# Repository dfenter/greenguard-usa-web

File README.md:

# greenguard-usa-web
website repository

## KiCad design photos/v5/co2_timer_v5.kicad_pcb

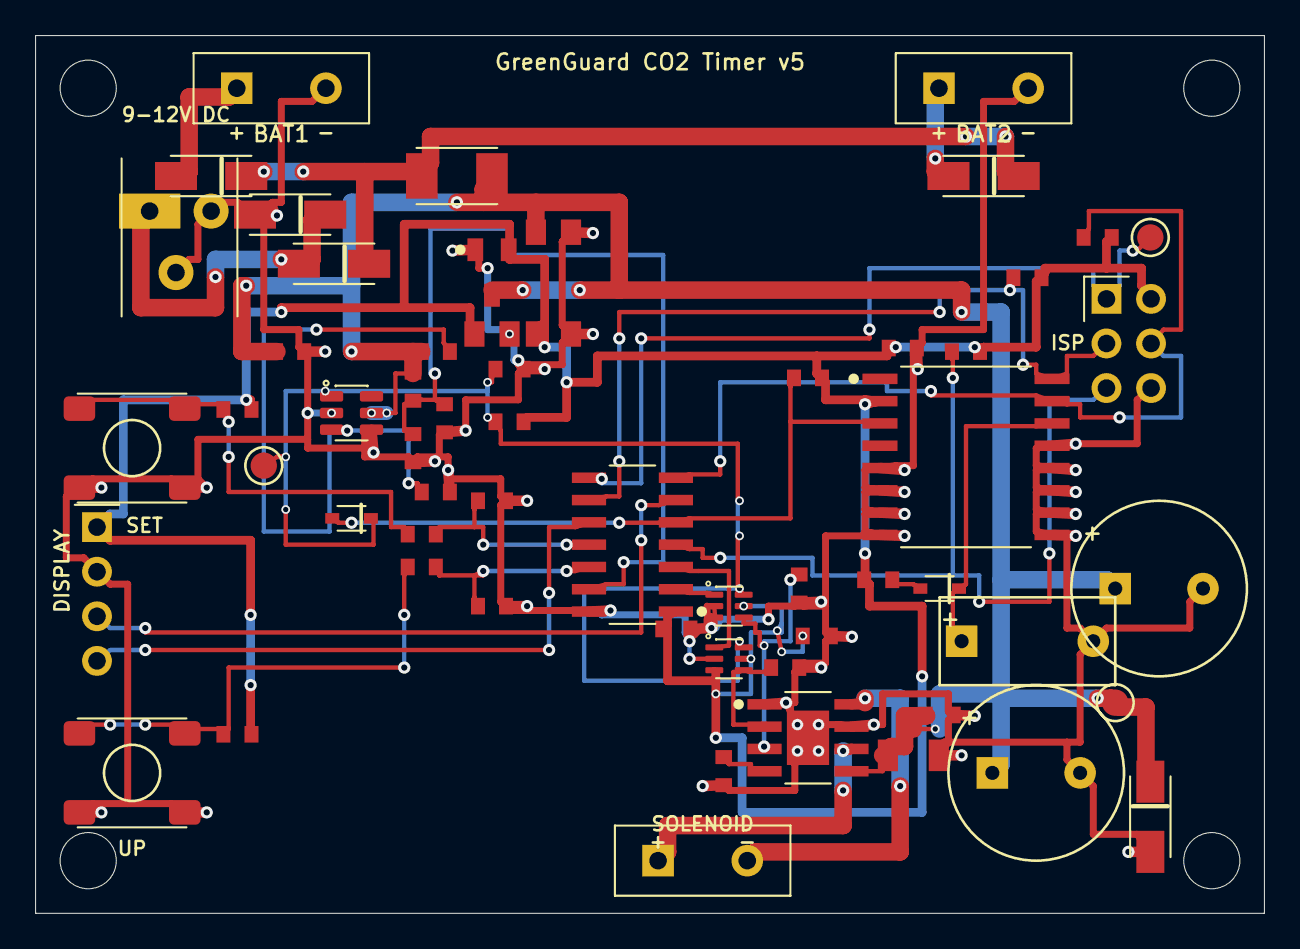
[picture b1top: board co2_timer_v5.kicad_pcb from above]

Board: 2 copper layers, 70.0 x 50.0 mm, 63 parts (0 on the bottom side), 30 nets.

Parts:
C1, C19: 1000uF; CP_Radial_D10.0mm_P5.00mm
C2, C3: 1uF; C_0805_2012Metric
C4: 10uF; C_1206_3216Metric
C5, C6, C7, C9, C10, C11, C14, C18: 100nF; C_0603_1608Metric
C12: 10uF; C_0805_2012Metric
D1, D4, D5: SS34; D_SMA
D2, D3: BAT54; D_SOD-323
F1: PPTC 1.1A MF-R110; Fuse_1812_4532Metric
H1, H2, H3, H4: MountingHole_3.2mm_M3
J1: BAT1_9V; PhoenixContact_MKDS_1,5_2-5.08mm_Angled
J2: SOLENOID; PhoenixContact_MKDS_1,5_2-5.08mm_Angled
J3: ISP; PinHeader_2x03_P2.54mm_Vertical
J4: DISPLAY; PinHeader_1x04_P2.54mm_Vertical
J5: DC_9-12V; BarrelJack_CUI_PJ-002A
J6: BAT2_9V; PhoenixContact_MKDS_1,5_2-5.08mm_Angled
R1, R2, R3, R4, R11, R12, R18: 10K; R_0603_1608Metric
R5: 220R; R_0603_1608Metric
R6: 43K 1%; R_0603_1608Metric
R7, R14, R15, R17: 100K; R_0603_1608Metric
R8: 33K; R_0603_1608Metric
R9, R10: 100R; R_0603_1608Metric
R13: 180K 1%; R_0603_1608Metric
R16: 10K 1%; R_0603_1608Metric
SC1: 0.1F_5V5; CP_CHP_10x5_P7.50mm
SW1: UP; PTS645SM43SMTR92LFS
SW2: SET; PTS645SM43SMTR92LFS
TP1: MISO; TestPoint_Pad_D1.5mm
TP2: /VM_OK; TestPoint_Pad_D1.5mm
TP3: VM; TestPoint_Pad_D1.5mm
TVS1, TVS2: SMAJ15A; D_SMA
U1: ATtiny84A; SOIC-14_3.9x8.7mm_P1.27mm
U2: DS3231M; SO-16_W7.5mm_P1.27mm
U3: MCP1703A-3.3; SOT-23
U4: DRV8871; HSOP-8_3.9x4.9mm_P1.27mm_PowerPAD
U5: TPS3700; SOT-23-6
U6: 3157_IN1; SOT-363_SC-70-6
U7: 3157_IN2; SOT-363_SC-70-6

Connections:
+3V3: C3.1, C6.1, C7.1, C12.1, C18.1, J3.2, J4.1, R1.2, R2.2, R3.2, R4.2, R5.1, R11.2, R12.2, R18.2, U1.1, U2.2, U3.2, U6.5, U7.3, U7.5
/ALERT: D3.A, R4.1, U1.5, U2.3
/RESET: J3.5, R1.1, U1.4
/VM_OK: D3.K, R17.1, R18.1, TP2.1, U5.1, U6.6, U7.6
BTN_SET: C11.1, R10.2, U1.11
BTN_SET_SW: R10.1, R12.1, SW2.1, SW2.2
BTN_UP: C10.1, R9.2, U1.12
BTN_UP_SW: R9.1, R11.1, SW1.1, SW1.2
DRV_IN1: R14.1, U4.3, U6.4
DRV_IN1_MCU: U1.2, U6.1
DRV_IN2: R15.1, U4.2, U7.4
DRV_IN2_MCU: U1.3, U7.1
GND: C1.-, C2.2, C3.2, C4.2, C5.2, C6.2, C7.2, C9.2, C10.2, C11.2, C12.2, C14.2, C18.2, C19.-, J1.2, J3.6, J4.2, J5.2, J5.3, J6.2, R6.2, R8.2, R14.2, R15.2, R16.2, R17.2, SC1.-, SW1.3, SW1.4, SW2.3, SW2.4, TVS1.A, TVS2.A, U1.14, U2.5, U2.6, U2.7, U2.8, U2.9, U2.10, U2.11, U2.12, U2.13, U3.1, U4.1, U4.7, U4.PAD, U5.2, U5.4, U6.2, U6.3, U7.2
ILIM: R6.1, U4.4
MISO: J3.1, TP1.1, U1.8
SCL: J3.3, R3.1, U1.9, U2.16
SDA: J3.4, R2.1, U1.7, U2.15
SOL_OUT1: J2.1, U4.6
SOL_OUT2: J2.2, U4.8
TM_CLK: J4.4, U1.10
TM_DIO: J4.3, U1.6
VBAT1_IN: D1.A, J1.1
VBAT2_IN: D5.A, J6.1
VBAT_CHG: D2.A, R5.2
VBAT_RTC: D2.K, SC1.+, U2.14
VIN_DC: D4.A, J5.1, TVS1.K
VIN_OR: D1.K, D4.K, D5.K, F1.1
VM: C1.+, C2.1, C4.1, C5.1, C9.1, C19.+, F1.2, R7.1, R13.1, TP3.1, TVS2.K, U3.3, U4.5, U5.5
VM_DIV: R13.2, R16.1, U5.3
VM_SENSE: C14.1, R7.2, R8.1, U1.13

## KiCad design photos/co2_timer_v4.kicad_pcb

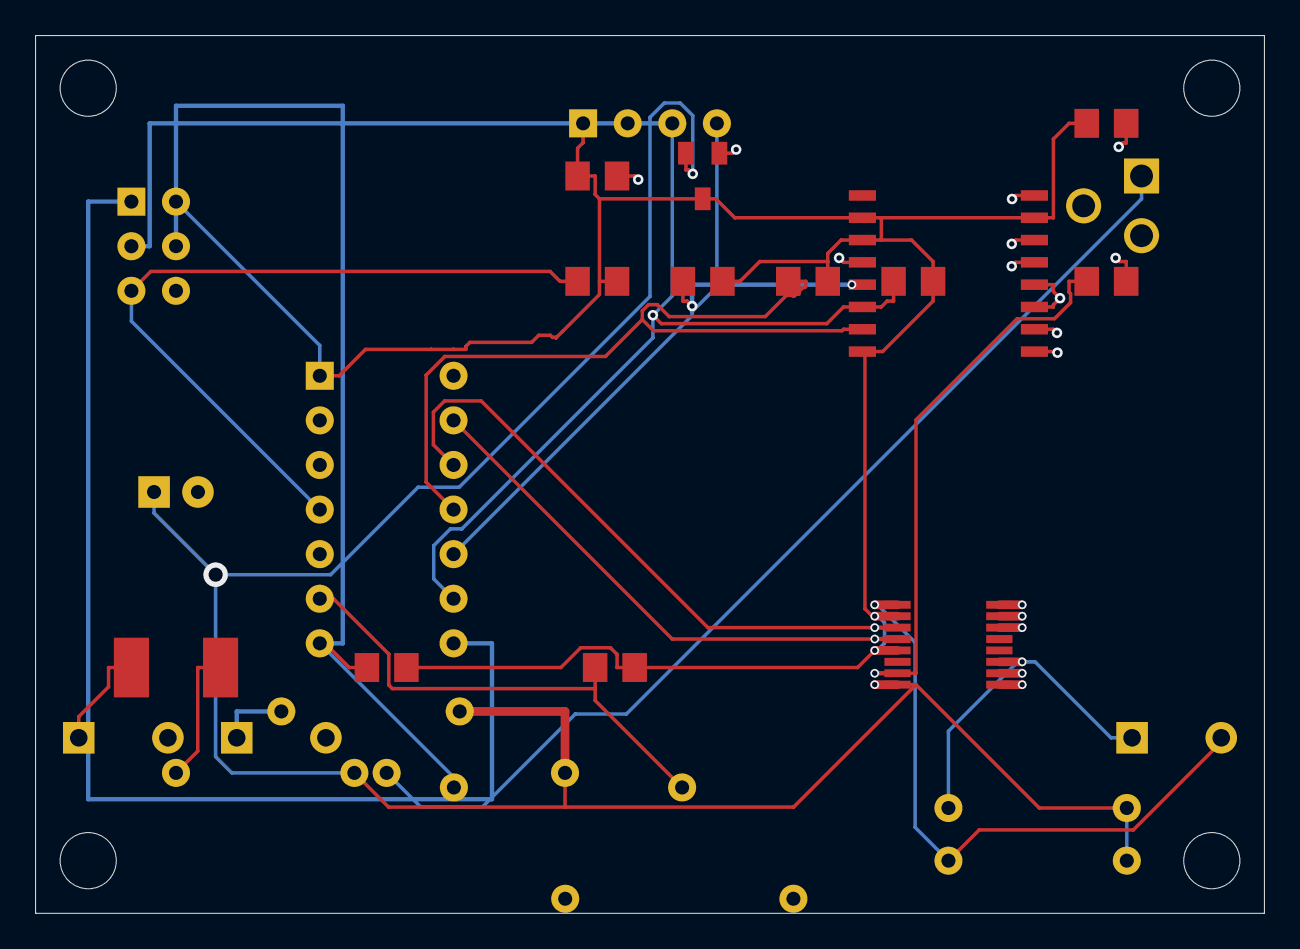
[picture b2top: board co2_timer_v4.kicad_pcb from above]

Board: 2 copper layers, 70.0 x 50.0 mm, 32 parts (0 on the bottom side), 19 nets.

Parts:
C1: 100uF 16V; CP_Radial_D6.3mm_P2.50mm
C2, C3: 100nF; C_0805_2012Metric
C4: 100nF_VCP; C_0805_2012Metric
D1, D2, D3, D4, D5: 1N4007; D_DO-41_SOD81_P10.16mm_Horizontal
F1: Polyfuse 1A; Fuse_1812_4532Metric
H1, H2, H3, H4: MountingHole_3.2mm_M3
J1: 9V_BATTERY; PhoenixContact_MKDS_1,5_2-5.08mm_Angled
J2: SOLENOID; PhoenixContact_MKDS_1,5_2-5.08mm_Angled
J3: ICSP; PinHeader_2x03_P2.54mm_Vertical
J4: TM1637; PinHeader_1x04_P2.54mm_Vertical
J5: DC_9-12V; BarrelJack_CUI_PJ-002A
J6: 9V_BATTERY_2; PhoenixContact_MKDS_1,5_2-5.08mm_Angled
R1: 10K_RESET; R_0805_2012Metric
R2: 10K_BTN_UP; R_0805_2012Metric
R3: 10K_BTN_SET; R_0805_2012Metric
R5: 4K7_SDA; R_0805_2012Metric
R6: 10K_INT; R_0805_2012Metric
R7: 4K7_SCL; R_0805_2012Metric
SW1: UP; SW_PUSH_6mm
SW2: SET; SW_PUSH_6mm
U1: ATtiny84A-20PU; DIP-14_W7.62mm
U2: DS3231M; SO-16_W7.5mm_P1.27mm
U3: MCP1703A-3302E; SOT-23
U4: DRV8833PWP; TSSOP-16_4.4x5mm_P0.65mm

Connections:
/RESET: J3.5, R1.1, U1.4
AOUT1: D2.A, J2.1, U4.11
AOUT2: D3.A, J2.2, U4.1
BARREL: D4.A, J5.1
BAT1: F1.1, J1.1
BAT1_FUSED: D1.A, F1.2
BAT2: D5.A, J6.1
BTN_SET: R3.1, SW2.1, U1.6
BTN_UP: J3.4, R2.1, SW1.1, U1.7
GND: C1.-, C2.2, C3.2, C4.2, J1.2, J3.6, J4.2, J5.2, J6.2, SW1.2, SW2.2, U1.14, U2.4, U2.9, U2.10, U2.11, U2.12, U2.13, U2.14, U2.16, U3.2, U4.9, U4.10, U4.14, U4.15, U4.16
IN1: U1.13, U4.4
IN2: U1.12, U4.3
INT: R6.1, U1.11, U2.7
MISO: J3.1, U1.8
SCL: J3.3, J4.3, R7.1, U1.9, U2.6
SDA: J4.4, R5.1, U1.10, U2.5
VCC: C2.1, C3.1, J3.2, J4.1, R1.2, R2.2, R3.2, R5.2, R6.2, R7.2, U1.1, U2.2, U2.3, U2.8, U2.15, U3.3, U4.2, U4.5
VCP: C4.1, U4.7
VIN: C1.+, D1.K, D2.K, D3.K, D4.K, D5.K, U3.1, U4.8

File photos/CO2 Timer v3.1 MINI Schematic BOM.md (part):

# GreenGuard CO2 Trap Timer — Rev 3.1 "Mini"

## Smallest build that meets all current (Rev 3.0) requirements

### Schedule ON 05:30 / OFF 23:30 | TM1637 display | 2-button set | latching solenoid | 9V battery + DC barrel jack | IP65

-----

## Design goal

Rev 3.0 works but is sized by through-hole parts and redundant features, not by
the actual requirements. Rev 3.1 keeps **every functional requirement** and the
**exact ATtiny84A pinout (zero firmware change)** while cutting the board from
70×50 mm to **45×30 mm** and the enclosure from 100×68×50 mm to **~83×58×33 mm**.

### Requirements held constant (nothing dropped)

| Requirement | Rev 3.0 | Rev 3.1 Mini |
|-------------|---------|--------------|
| Schedule ON 05:30 / OFF 23:30, user-settable | ✅ | ✅ (same firmware) |
| RTC timekeeping survives reboot | DS3231M | DS3231M (unchanged) |
| TM1637 4-digit display, on-demand wake | ✅ | ✅ (unchanged) |
| 2-button time set | ✅ | ✅ (unchanged) |
| 12V bistable latching solenoid drive | DRV8833 | DRV8833 (unchanged) |
| ≥7-month battery life | ~7 mo (1× 9V) | ~7 mo (1× 9V) |
| Dual power (battery + barrel jack) | ✅ | ✅ |
| IP65 weatherproof, CO2 in/out barbs | ✅ | ✅ |

-----

## What changed from Rev 3.0 (size only — no function lost)

| Item | Rev 3.0 | Rev 3.1 Mini | Size win |
|------|---------|--------------|----------|
| MCU package | ATtiny84A **DIP-14** | ATtiny84A **SOIC-14** | same silicon/pinout, ~70% smaller footprint, **no firmware change** |
| Reverse-pol / OR diodes | 3× 1N4007 **DO-41** (D1/D4/D5) | 2× SS14 **SMA** Schottky (D1/D4) | DO-41 is ~5×9 mm each; SMA is 5×2.6 mm. Also lower Vf |
| Flyback diodes | 2× 1N4007 DO-41 (D2/D3) | **removed** | DRV8833 has internal body diodes; latching pulse is 50 ms coast-to-brake. External flyback unnecessary |
| Second 9V battery | J6 screw term + D5 OR-diode | **removed** | 1× 9V already meets the 7-month spec; redundant pack drove enclosure depth |
| Battery / solenoid connectors | 3× 5.08 mm screw terminals | 3× **JST-PH 2-pin** (or solder pads) | 5.08 mm pitch is the single biggest edge-hog |
| Bulk cap | 100 µF THT radial | 100 µF **SMD electrolytic** (6.3 mm can) | frees a tall through-hole footprint |
| Buttons | 6×6 mm THT | 4.5×4.5 mm SMD side/right-angle (or panel-mount via flylead) | |
| Resistors/caps | 0805 | 0603 | minor |
| LDO | MCP1703A SOT-23 | MCP1703A SOT-23 (unchanged) | already small |
| PCB | 70×50 mm, 2-layer | **45×30 mm**, 2-layer | ~62% area reduction |
| Enclosure | 100×68×50 mm | **~83×58×33 mm** IP65 ABS | depth set by 9V battery (17 mm) + PCB on 6 mm standoffs |

-----

## Schematic — net list (Rev 3.1)

Identical topology to Rev 3.0 minus the second battery and the two flyback
diodes. **ATtiny84A pin assignment is unchanged**, so `co2_timer_v3.ino`
flashes as-is.

### Power

```
9V Battery (+)  → [F1 Polyfuse 1A] → [D1 SS14 Schottky] → VIN_PROTECTED
DC Barrel Jack(+) →                  [D4 SS14 Schottky] → VIN_PROTECTED   (OR — higher source wins)
VIN_PROTECTED → [C1 100µF SMD] → GND
VIN_PROTECTED → [U3 MCP1703A-3302E] → VCC 3.3V → MCU, RTC, display, DRV8833 logic
VIN_PROTECTED → VM rail → DRV8833 H-bridge output (solenoid)
GND → common
```

### ATtiny84A (U1, SOIC-14) — UNCHANGED pinout

```
Pin 1  VCC      ── 3.3V
Pin 2  PB0      ── ICSP MOSI
Pin 3  PB1      ── ICSP MISO
Pin 4  PB3/RST  ── [R1 10k] ── VCC
Pin 5  PB2      ── ICSP SCK
Pin 6  PA7      ── [R3 10k] ── BTN_SET (SW2) ── GND
Pin 7  PA6      ── [R2 10k] ── BTN_UP (SW1) ── GND
Pin 8  PA5      ── (spare)
Pin 9  PA4      ── TM1637 CLK / DS3231 SCL (soft I2C)
Pin 10 PA3      ── TM1637 DIO / DS3231 SDA (soft I2C)
Pin 11 PA2      ── [R6 10k] ── DS3231 INT (PCINT2)
Pin 12 PA1      ── DRV8833 IN2 (CLOSE)
Pin 13 PA0      ── DRV8833 IN1 (OPEN)
Pin 14 GND      ── GND
```

### DRV8833 (U4) — solenoid drive, UNCHANGED

```
AIN1←PA0  AIN2←PA1  AOUT1→coil(+)  AOUT2→coil(-)
VM←VIN_PROTECTED  VCC←3.3V  nSLEEP←VCC  VCP─[C4 100nF]─GND
OPEN  : AIN1=1,AIN2=0 50ms → coast
CLOSE : AIN1=0,AIN2=1 50ms → coast
Internal body diodes handle coil flyback (D2/D3 removed).
```

### DS3231M (U2) and TM1637 — UNCHANGED from Rev 3.0

```
DS3231M: VCC/VBAT←3.3V  SDA←PA3  SCL←PA4  INT─[R6 10k]─PA2
TM1637 : VCC←3.3V  CLK←PA4  DIO←PA3  (4-pin header J4)
I2C pullups: [R5 4.7k] SDA→VCC, [R7 4.7k] SCL→VCC
```

-----

## Bill of Materials — PCB (Rev 3.1)

| Ref | Description | Value | Package | Qty | Unit $ | Ext $ |
|-----|-------------|-------|---------|-----|--------|-------|
| U1 | MCU | ATtiny84A-SSU | **SOIC-14** | 1 | $1.20 | $1.20 |
| U2 | RTC | DS3231M | SO-16 | 1 | $0.80 | $0.80 |
| U3 | LDO 2µA Iq | MCP1703A-3302E | SOT-23-3 | 1 | $0.25 | $0.25 |
| U4 | H-bridge | DRV8833PWP | HTSSOP-16 | 1 | $0.35 | $0.35 |
| D1 | Reverse-pol OR | SS14 Schottky | **SMA** | 1 | $0.04 | $0.04 |
| D4 | Barrel-jack OR | SS14 Schottky | **SMA** | 1 | $0.04 | $0.04 |
| SW1 | UP button | 4.5×4.5 SMD tactile | SMD | 1 | $0.04 | $0.04 |
| SW2 | SET button | 4.5×4.5 SMD tactile | SMD | 1 | $0.04 | $0.04 |
| F1 | Polyfuse | 1A/2A trip | 1206 SMD | 1 | $0.18 | $0.18 |
| R1,R2,R3,R6 | Pullups | 10kΩ | 0603 | 4 | $0.01 | $0.04 |
| R5,R7 | I2C pullups | 4.7kΩ | 0603 | 2 | $0.01 | $0.02 |
| C1 | Bulk | 100µF 16V | SMD elec 6.3mm | 1 | $0.08 | $0.08 |
| C2,C3,C4 | Decoupling | 100nF | 0603 | 3 | $0.01 | $0.03 |
| J1 | Battery in | JST-PH 2P | SMD/THT | 1 | $0.08 | $0.08 |
| J2 | Solenoid out | JST-PH 2P | SMD/THT | 1 | $0.08 | $0.08 |
| J3 | ICSP | 2×3 1.27mm or Tag-Connect pads | SMD | 1 | $0.05 | $0.05 |
| J4 | TM1637 header | 1×4 2.54mm | THT | 1 | $0.08 | $0.08 |
| J5 | DC barrel jack | 5.5/2.1mm PCB | THT | 1 | $0.20 | $0.20 |
| **PCB TOTAL** | | | | | | **~$3.71** |

Removed vs Rev 3.0: D2, D3, D5 (three DO-41 diodes), J6 (2nd battery screw term).
Net BOM is cheaper **and** smaller.

### Off-board / mechanical

| Item | Spec | Unit $ |
|------|------|--------|
| TM1637 display module | 4-digit 0.36" red | $0.50 |
| Bistable latching solenoid | 12V 1/4" NPT Viton | $8.00 |
| IP65 ABS enclosure | **~83×58×33 mm** (Gainta G203 / equiv) | $2.50 |
| Brass barb bulkheads 1/4"NPT 6mm ×2 | | $1.50 |
| DC barrel jack panel-mount, capped | 5.5/2.1 weatherproof | $0.80 |
| 9V battery snap, PCB lead ×1 | | $0.80 |
| M3 brass standoffs 6mm ×4 | | $1.00 |
| Hook-up wire 22AWG | | $0.50 |
| **MECH TOTAL** | | **~$15.60** |

### Unit cost by volume

| Volume | PCB+Asm | Mech | Labor | Total | Margin @ $89.99 |
|--------|---------|------|-------|-------|-----------------|
| 10 (proto) | $10.00 | $20.00 | — | **~$30** | 67% |
| 100 | $5.00 | $15.60 | $4.50 | **~$25** | 72% |
| 500 | $3.80 | $11.00 | $2.50 | **~$17** | 81% |

-----

## PCB layout (45×30 mm, 2-layer)

```
┌─────────────────────────────────────────────┐ 45mm
│ J5 barrel   J1 batt        J2 solenoid       │
│   ▢           ▢                ▢             │
│  [U2 DS3231]   [U1 ATtiny84A]  [U4 DRV8833]  │
│  [C1] D1 D4 F1   R's/C's        VCP C4       │  30mm
│  J4 TM1637 hdr   J3 ICSP pads                │
│  SW1 ○        SW2 ○   (or panel flyleads)    │
└─────────────────────────────────────────────┘
```

Mounting: 4× M3 holes, 3 mm inset from corners. Stretch target 40×28 mm if
buttons are moved to panel-mount flyleads and ICSP uses Tag-Connect pads.

-----

## Enclosure drilling — ~83×58×33 mm IP65 ABS

Depth note: interior usable ≈ 28 mm. 9V battery (17 mm) lies flat on the base;
PCB sits on 6 mm standoffs above it. Front lid carries the display + buttons.

```
FRONT LID (83×58)            LEFT (58×33)        RIGHT (58×33)
┌───────────────────────┐    ┌────────────┐      ┌────────────┐
│  ┌─────────────────┐  │    │            │      │            │
│  │ 40×14 display   │  │    │  ◎ CO2 IN  │      │  CO2 OUT ◎ │
│  └─────────────────┘  │    │ [29,16]    │      │   [29,16]  │
│     ○ UP    ○ SET     │    └────────────┘      └────────────┘
│  [28,42]   [55,42]    │      12mm barb           12mm barb
└───────────────────────┘
   BACK (83×58): ◉ barrel jack [41,29], 12mm, weatherproof cap
```

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
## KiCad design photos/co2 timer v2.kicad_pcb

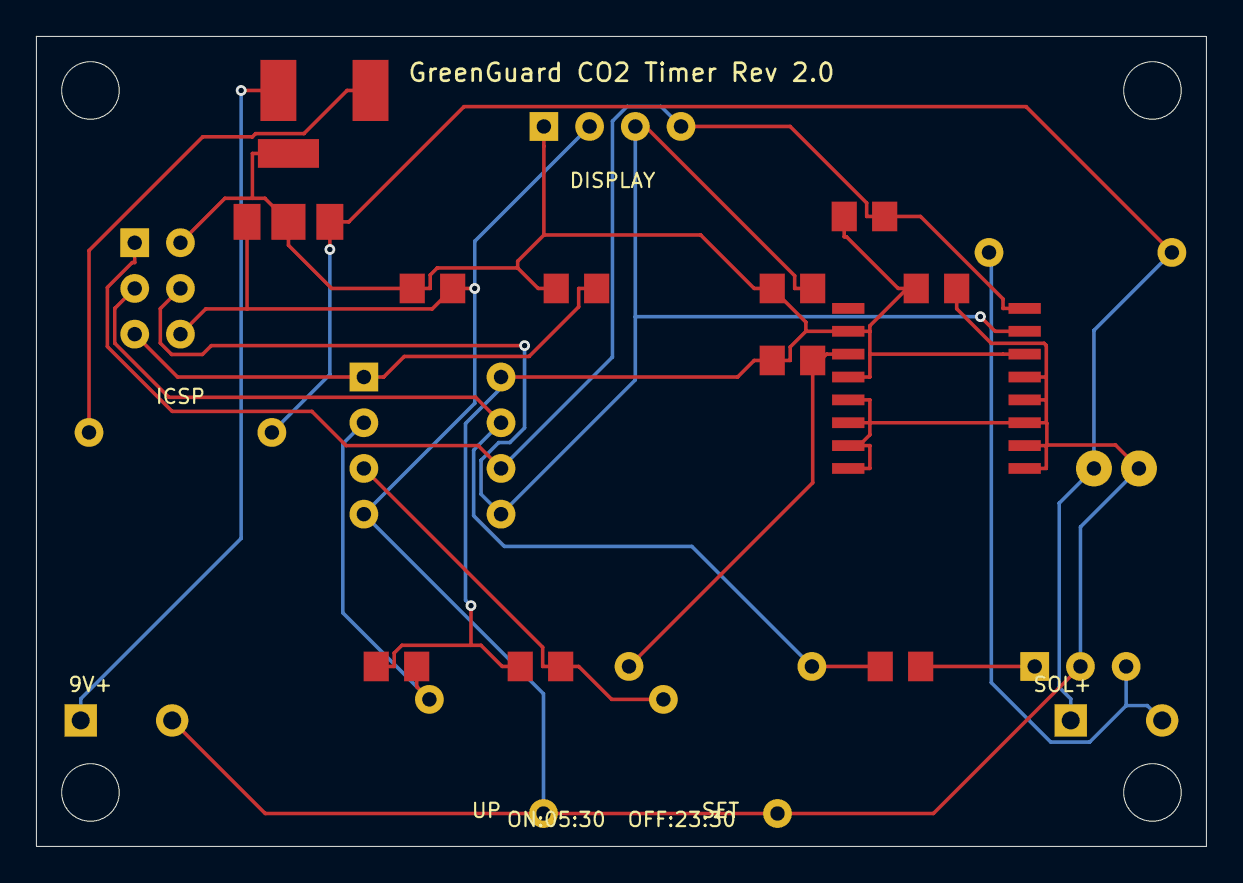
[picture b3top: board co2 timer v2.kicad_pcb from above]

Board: 2 copper layers, 65.0 x 45.0 mm, 28 parts (0 on the bottom side), 14 nets.

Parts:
C1: 100uF_16V; CP_Radial_D6.3mm_P2.50mm
C2: 100nF_U1; C_0805_2012Metric
C3: 100nF_U2; C_0805_2012Metric
D1: 1N4007; D_DO-41_SOD81_P10.16mm_Horizontal
D2: 1N4007_INT; D_DO-41_SOD81_P10.16mm_Horizontal
D3: 1N4007_FLYBACK; D_DO-41_SOD81_P10.16mm_Horizontal
F1: 1A_Polyfuse; Fuse_1812_4532Metric
H1, H2, H3, H4: MountingHole_3.2mm_M3
J1: 9V_IN; PhoenixContact_MKDS_1,5_2-5.08mm_Angled
J2: SOLENOID; PhoenixContact_MKDS_1,5_2-5.08mm_Angled
J3: ICSP; PinHeader_2x03_P2.54mm_Vertical
J4: TM1637; PinHeader_1x04_P2.54mm_Vertical
Q1: IRL540NPBF; TO-220-3_Vertical
R1: 10K_RESET; R_0805_2012Metric
R2: 10K_BTN_UP; R_0805_2012Metric
R3: 10K_BTN_SET; R_0805_2012Metric
R4: 100R_GATE; R_0805_2012Metric
R5: 4K7_SDA; R_0805_2012Metric
R6: 10K_INT; R_0805_2012Metric
R7: 4K7_SCL; R_0805_2012Metric
SW1: UP; SW_PUSH_6mm
SW2: SET; SW_PUSH_6mm
U1: ATtiny85-20PU; DIP-8_W7.62mm
U2: DS3231SN; SO-16_W7.5mm_P1.27mm
U3: AMS1117-3.3; SOT-223-3_TabPin2

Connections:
+3V3: C2.1, C3.1, J3.2, J4.1, R1.1, R2.1, R3.1, R5.1, R6.1, R7.1, U1.8, U2.2, U2.4, U2.14, U3.2
+9V_RAW: C1.+, D1.K, D3.K, J2.1, U3.3
BATT_RAW: F1.1, J1.1
BTN_SET: R3.2, SW2.1, U1.3
BTN_UP: R2.2, SW1.1, U1.2
D1_ANODE: D1.A, F1.2
GATE_NET: Q1.1, R4.2
GND: C1.-, C2.2, C3.2, J1.2, J3.6, J4.2, Q1.2, SW1.2, SW2.2, U1.4, U2.5, U2.6, U2.7, U2.8, U2.9, U2.10, U2.11, U2.12, U2.13, U3.1
PB2_CTRL: D2.K, J3.3, R4.1, U1.7
RESET_N: J3.5, R1.2, U1.1
RTC_INT: D2.A, R6.2, U2.3
SCL_DIO: J3.1, J4.4, R7.2, U1.6, U2.16
SDA_CLK: J3.4, J4.3, R5.2, U1.5, U2.15
SOLENOID_DRAIN: D3.A, J2.2, Q1.3

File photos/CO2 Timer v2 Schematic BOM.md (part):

# GreenGuard CO2 Trap Timer — Rev 2.0

## Schematic & Bill of Materials

### Schedule: ON 5:30 AM / OFF 11:30 PM | TM1637 Display | 2-Button Time Set | No CR2032

-----

## What Changed from Rev 1.0

|Item        |Rev 1.0                    |Rev 2.0                     |
|------------|---------------------------|----------------------------|
|Display     |None (LED blink feedback)  |TM1637 4-digit 7-segment    |
|Time setting|Single button + blink count|2-button UP/SET with display|
|Buttons     |1x tactile                 |2x tactile                  |
|RTC backup  |CR2032 coin cell           |3.3V rail (no coin cell)    |
|Status LEDs |2x (power + valve)         |Removed — display shows time|
|Net BOM cost|~$4.30/board               |~$4.05/board                |

-----

## Schematic — Net List

### Power

Two input options share the J1 screw terminal — only one should be connected at a time:

```
Option A — 9V Battery:
  9V Battery (+) via snap connector ──> J1(+)

Option B — DC Wall Adapter:
  120V AC wall adapter (9V DC output, 500 mA min, center-positive)
  ──> Rear-panel barrel jack (5.5 mm / 2.1 mm) ──> pigtail wires ──> J1(+/−)

Both options:
  J1(+) ──> [F1 Polyfuse 1A] ──> [D1 1N4007] ──> VIN_PROTECTED
  VIN_PROTECTED ──> [U3 AMS1117-3.3] ──> VCC (3.3V) ──> MCU, RTC, Display
  VIN_PROTECTED ──> RAW_9V rail ──> Solenoid (+)
  GND ──> Common ground
```

### ATtiny85 (U1) Pin Assignment

```
Pin 1  PB5/RESET  ── [R1 10kΩ] ── VCC
Pin 2  PB3        ── [R2 10kΩ pullup] ── BTN_UP (SW1) ── GND
Pin 3  PB4        ── [R3 10kΩ pullup] ── BTN_SET (SW2) ── GND
Pin 4  GND        ── GND
Pin 5  PB0        ── TM1637 CLK  (also DS3231 SDA via soft I2C — see note)
Pin 6  PB1        ── TM1637 DIO  (also DS3231 SCL via soft I2C — see note)
Pin 7  PB2        ── [R4 100Ω] ── MOSFET Gate (Q1)
                  ── DS3231 INT (via [D2 1N4007] diode isolation — see note)
Pin 8  VCC        ── 3.3V
```

> **Pin-sharing note — bench validation required before production:**
> PB0 and PB1 are shared between the TM1637 display (bit-bang protocol) and the DS3231 RTC (software I2C). The firmware serializes all bus access — only one device is addressed at a time — but this shared-bus scheme relies on correct firmware timing and idle-state behavior. D2 (1N4007, cathode to PB2) prevents DS3231 INT from inadvertently asserting the MOSFET gate: when PB2 drives HIGH (valve open), D2 is reverse-biased and INT cannot pull the gate down; when PB2 is LOW (valve closed), INT may also pull LOW, which is harmless. Both shared-pin arrangements require bench validation on assembled hardware before committing to production quantities. If contention is observed, the recommended upgrade path is ATtiny1616/1626 (14 pins, dedicated hardware I2C, drop-in for this application).

### DS3231 RTC (U2)

```
VCC  ── 3.3V
GND  ── GND
SDA  ── ATtiny85 PB0 (shared with TM1637 CLK via soft I2C) ── [R5 4.7kΩ] ── VCC
SCL  ── ATtiny85 PB1 (shared with TM1637 DIO via soft I2C) ── [R7 4.7kΩ] ── VCC
INT  ── ATtiny85 PB2 via D2 1N4007 (cathode to PB2, anode to INT) ── [R6 10kΩ] ── VCC
VBAT ── 3.3V (no coin cell — powered from main rail)
32K  ── NC
```

### TM1637 Display Module

```
VCC ── 3.3V
GND ── GND
CLK ── ATtiny85 PB0
DIO ── ATtiny85 PB1
```

### Solenoid Driver

```
ATtiny85 PB2 ── [R4 100Ω] ── MOSFET Gate (Q1: IRL540N)
                              MOSFET Source ── GND
                              MOSFET Drain  ── Solenoid (-)
                              Solenoid (+)  ── RAW_9V

[D3 1N4007] Cathode ── RAW_9V
            Anode   ── MOSFET Drain  (flyback protection)

[C1 100µF 16V] across RAW_9V and GND near solenoid
```

### Decoupling

```
[C2 100nF] across VCC and GND near U1
[C3 100nF] across VCC and GND near U2
```

-----

## Bill of Materials

### PCB Components

|Ref          |Description      |Value               |Package   |LCSC # |Qty|Unit $|Ext $     |
|-------------|-----------------|--------------------|----------|-------|---|------|----------|
|U1           |Microcontroller  |ATtiny85-20PU       |DIP-8     |C89852 |1  |$1.20 |$1.20     |
|U2           |RTC              |DS3231SN            |SO-16     |C9868  |1  |$1.50 |$1.50     |
|U3           |LDO Regulator    |AMS1117-3.3         |SOT-223   |C6186  |1  |$0.15 |$0.15     |
|Q1           |N-Ch MOSFET      |IRL540NPBF          |TO-220    |C60330 |1  |$0.45 |$0.45     |
|D1           |Reverse polarity |1N4007              |DO-41     |C727110|1  |$0.05 |$0.05     |
|D2           |RTC INT isolation|1N4007              |DO-41     |C727110|1  |$0.05 |$0.05     |
|D3           |Flyback          |1N4007              |DO-41     |C727110|1  |$0.05 |$0.05     |
|SW1          |UP Button        |6x6mm Tactile       |THT       |C318884|1  |$0.05 |$0.05     |
|SW2          |SET Button       |6x6mm Tactile       |THT       |C318884|1  |$0.05 |$0.05     |
|F1           |Polyfuse         |1A / 2A trip        |1812 SMD  |C369150|1  |$0.20 |$0.20     |
|R1           |RESET pullup     |10kΩ                |0805      |C17414 |1  |$0.01 |$0.01     |
|R2           |BTN_UP pullup    |10kΩ                |0805      |C17414 |1  |$0.01 |$0.01     |
|R3           |BTN_SET pullup   |10kΩ                |0805      |C17414 |1  |$0.01 |$0.01     |
|R4           |MOSFET gate      |100Ω                |0805      |C17408 |1  |$0.01 |$0.01     |
|R5           |I2C SDA pullup   |4.7kΩ               |0805      |C17673 |1  |$0.01 |$0.01     |
|R6           |INT pullup       |10kΩ                |0805      |C17414 |1  |$0.01 |$0.01     |
|R7           |I2C SCL pullup   |4.7kΩ               |0805      |C17673 |1  |$0.01 |$0.01     |
|C1           |Bulk cap         |100µF 16V           |THT radial|C62923 |1  |$0.10 |$0.10     |
|C2           |Decoupling       |100nF               |0805      |C49678 |1  |$0.01 |$0.01     |
|C3           |Decoupling       |100nF               |0805      |C49678 |1  |$0.01 |$0.01     |
|J1           |Power input (battery or adapter)|2P 5.08mm screw term|THT  |C8465  |1  |$0.15 |$0.15     |
|J2           |Solenoid output  |2P 5.08mm screw term|THT       |C8465  |1  |$0.15 |$0.15     |
|J3           |ICSP header      |2x3 2.54mm          |THT       |C124378|1  |$0.10 |$0.10     |
|J4           |Display connector|1x4 2.54mm          |THT       |C358686|1  |$0.10 |$0.10     |
|U1_SOCKET    |DIP-8 IC socket  |8-pin 0.3"          |THT       |—      |1  |$0.10 |$0.10     |
|**PCB TOTAL**|                 |                    |          |       |   |      |**~$4.26**|

### Off-Board / Mechanical Components

|Item                         |Spec                          |Source         |Unit $     |
|-----------------------------|------------------------------|---------------|-----------|
|TM1637 display module        |4-digit 7-seg, red, 0.36”     |Amazon / LCSC  |$1.50      |
|Solenoid valve               |US Solid 1/4” NPT NC 12V Viton; ~400 mA @ 12V; rated 0–100 PSI; NC (CO2 off when unpowered); flow bidirectional — verify inlet/outlet against regulator plumbing before assembly|Amazon         |$10.99     |
|IP65 ABS enclosure           |100x68x50mm                   |Amazon (Zulkit)|$7.99      |
|1/4” NPT to 6mm barb fittings|Brass x2                      |Amazon         |$3.50      |
|PG7 cable glands x2          |IP65 — CO2 inlet/outlet       |Amazon         |$2.00      |
|Panel-mount DC barrel jack   |5.5 mm OD / 2.1 mm ID, center-positive; mounts in rear face 12 mm hole; pigtail wired to J1 screw terminal|Amazon|$1.50|
|9V DC wall adapter           |120V AC input, 9V DC 1A min output, center-positive; **optional** — use instead of battery|Amazon|$8.00|
|9V battery snap connector    |PCB mount; use with 9V battery — **omit if using wall adapter**|Amazon|$1.00|
|M3 brass standoffs 10mm x4   |PCB mount                     |Amazon         |$2.00      |
|Hook-up wire 22AWG           |Solenoid leads + barrel jack pigtail|Shop stock |$1.00      |
|**MECHANICAL TOTAL (battery)**|                             |               |**~$31.48**|
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
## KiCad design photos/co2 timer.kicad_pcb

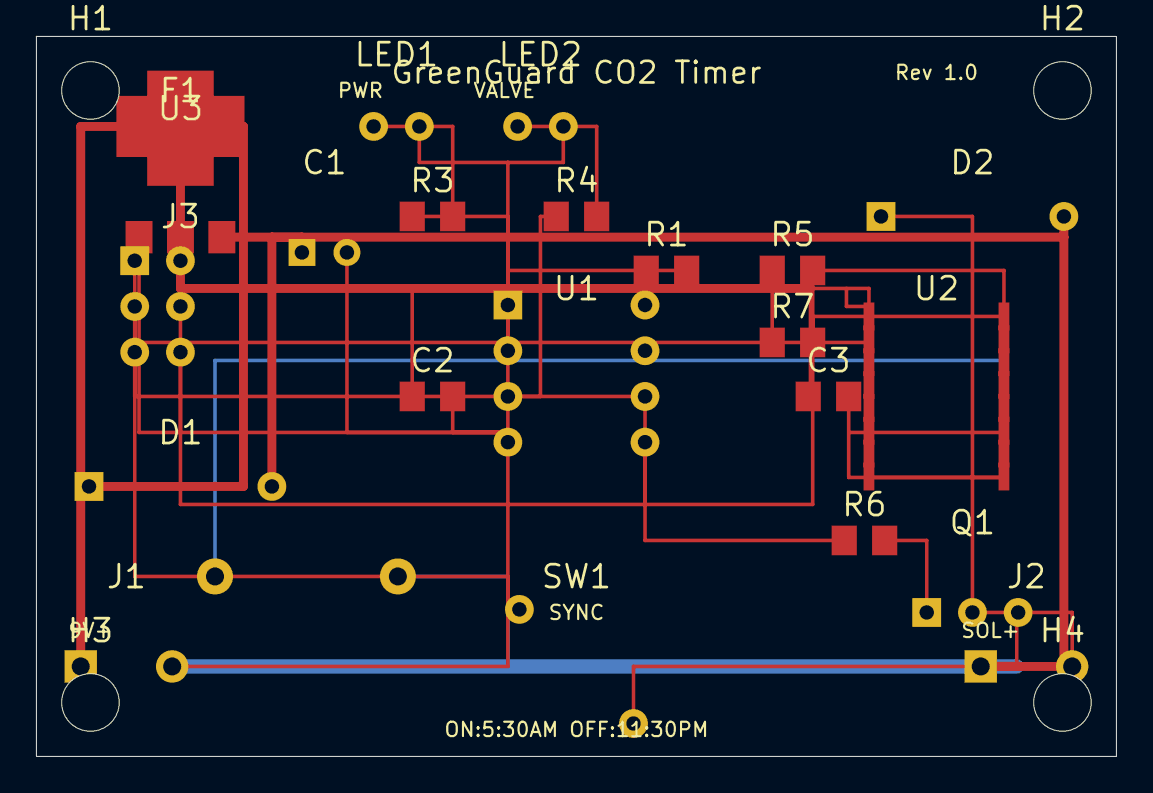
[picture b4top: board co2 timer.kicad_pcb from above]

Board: 2 copper layers, 60.0 x 40.0 mm, 27 parts (1 on the bottom side), 16 nets.

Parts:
BT1: CR2032; BatteryHolder_Keystone_3034_1x20mm
C1: 100uF_16V; CP_Radial_D6.3mm_P2.50mm
C2, C3: 100nF; C_0805_2012Metric
D1, D2: 1N4007; D_DO-41_SOD81_P10.16mm_Horizontal
F1: 1A_Polyfuse; Fuse_1812_4532Metric
H1, H2, H3, H4: MountingHole_3.2mm_M3
J1: 9V_IN; PhoenixContact_MKDS_1,5_2-5.08mm_Angled
J2: SOLENOID; PhoenixContact_MKDS_1,5_2-5.08mm_Angled
J3: ICSP; PinHeader_2x03_P2.54mm_Vertical
LED1: Green; LED_D3.0mm
LED2: Blue; LED_D3.0mm
Q1: IRL540NPBF; TO-220-3_Vertical
R1, R7: 10K; R_0805_2012Metric
R3, R4: 470R; R_0805_2012Metric
R5: 4K7; R_0805_2012Metric
R6: 100R; R_0805_2012Metric
SW1: SYNC; SW_PUSH_6mm
U1: ATtiny85-20PU; DIP-8_W7.62mm
U2: DS3231SN; SO-16_W7.5mm_P1.27mm
U3: AMS1117-3.3; SOT-223-3_TabPin2

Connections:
+3V3: C2.1, C3.1, J3.2, R1.1, R5.1, R7.1, U1.8, U2.2, U2.4, U3.2, U3.4
+9V: C1.1, D1.K, D2.K, J2.1, U3.3
+9V_FUSED: D1.A, F1.2
+9V_IN: F1.1, J1.1
GATE: Q1.1, R6.2
GND: BT1.-, C1.2, C2.2, C3.2, J1.2, J3.6, LED1.K, LED2.K, Q1.3, SW1.2, U1.4, U2.1, U2.5, U2.6, U2.7, U2.8, U2.9, U2.10, U2.11, U2.12, U2.13, U3.1
LED1_A: LED1.A, R3.2
LED2_A: LED2.A, R4.2
LED_PWR: R3.1, U1.2
LED_VALVE: R4.1, U1.3
MISO_SOL: J3.1, R6.1, U1.6
RESET_N: J3.5, R1.2, SW1.1, U1.1
SCL_INT: J3.3, R7.2, U1.7, U2.3, U2.16
SDA: J3.4, R5.2, U1.5, U2.15
SOL_RTN: D2.A, J2.2, Q1.2
VBAT: BT1.+, U2.14

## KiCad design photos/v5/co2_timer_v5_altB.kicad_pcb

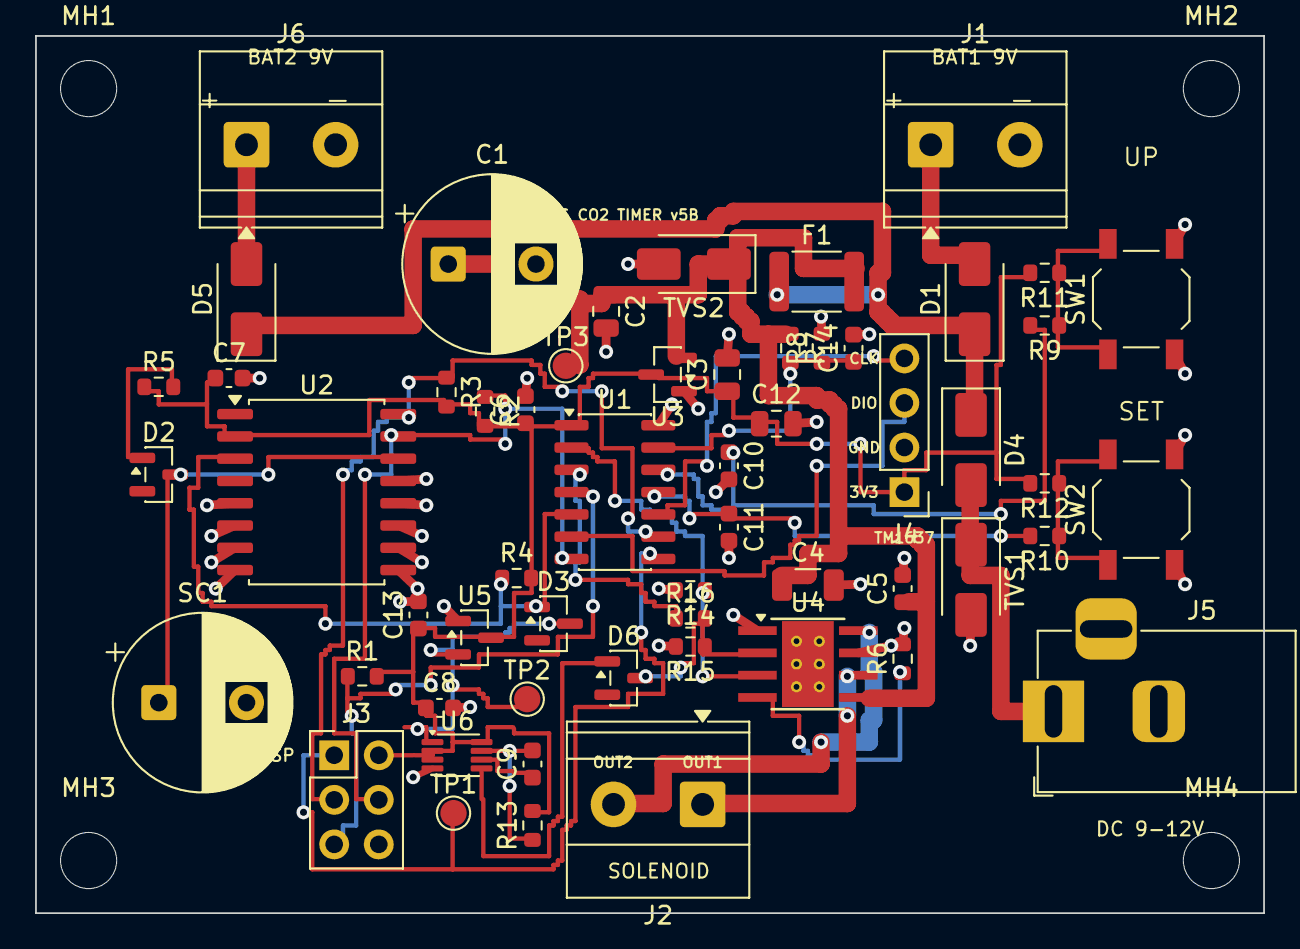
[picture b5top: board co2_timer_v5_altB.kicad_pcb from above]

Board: 2 copper layers, 70.0 x 50.0 mm, 61 parts (0 on the bottom side), 31 nets.

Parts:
C1: 470uF 16V; CP_Radial_D10.0mm_P5.00mm
C2, C3: 1uF; C_0805_2012Metric
C4: 10uF; C_1206_3216Metric
C5, C6, C7, C8, C10, C11, C13, C14: 100nF; C_0603_1608Metric
C9: 470nF; C_0603_1608Metric
C12: 10uF; C_0805_2012Metric
D1, D4, D5: SS34; D_SMA
D2, D3, D6: BAT54; SOT-23
F1: PPTC 1.1A; Fuse_1812_4532Metric
J1: BAT1 9V; TerminalBlock_Phoenix_MKDS-1,5-2-5.08_1x02_P5.08mm_Horizont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
J2: SOLENOID; TerminalBlock_Phoenix_MKDS-1,5-2-5.08_1x02_P5.08mm_Horizont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
J3: ISP; PinHeader_2x03_P2.54mm_Vertical
J4: TM1637; PinHeader_1x04_P2.54mm_Vertical
J5: DC 9-12V; BarrelJack_Horizontal
J6: BAT2 9V; TerminalBlock_Phoenix_MKDS-1,5-2-5.08_1x02_P5.08mm_Horizont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
MH1, MH2, MH3, MH4: MountingHole_3.2mm_M3
R1, R2, R3, R4, R11, R12: 10K; R_0603_1608Metric
R5: 220R; R_0603_1608Metric
R6: 43K; R_0603_1608Metric
R7, R13, R14, R15: 100K; R_0603_1608Metric
R8: 33K; R_0603_1608Metric
R9, R10: 100R; R_0603_1608Metric
R16: 1K; R_0603_1608Metric
SC1: 1F 5.5V; CP_Radial_D10.0mm_P5.00mm
SW1: UP; SW_SPST_TL3342
SW2: SET; SW_SPST_TL3342
TP1: MISO; TestPoint_Pad_D1.5mm
TP2: /SUPV; TestPoint_Pad_D1.5mm
TP3: VM; TestPoint_Pad_D1.5mm
TVS1, TVS2: SMAJ15A; D_SMA
U1: ATtiny84A-SSU; SOIC-14_3.9x8.7mm_P1.27mm
U2: DS3231M; SOIC-16W_7.5x10.3mm_P1.27mm
U3: MCP1703A-3.3; SOT-23
U4: DRV8871; Texas_HTSOP-8-1EP_3.9x4.9mm_P1.27mm_EP2.95x4.9mm_Mask2.4x3.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
U5: TPS3839G30; SOT-23
U6: 74LVC1G123; VSSOP-8_2.3x2mm_P0.5mm

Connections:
+3V3: C3.1, C6.1, C7.1, C8.1, C12.1, C13.1, J3.2, J4.1, R1.2, R2.2, R3.2, R4.2, R5.1, R11.2, R12.2, R13.2, U1.1, U2.2, U3.3, U5.3, U6.2, U6.3, U6.8
/ALERT: D3.1, R4.1, U1.5, U2.3
/RESET: J3.5, R1.1, U1.4
/SUPV: D3.3, TP2.1, U5.2, U6.1
BTN_SET: C11.1, R10.2, U1.11
BTN_SET_SW: R10.1, R12.1, SW2.1
BTN_UP: C10.1, R9.2, U1.12
BTN_UP_SW: R9.1, R11.1, SW1.1
DRV_IN1: R14.1, U1.2, U4.3
DRV_IN2: D6.3, R15.1, R16.2, U4.2
DRV_IN2_MCU: R16.1, U1.3
GND: C1.2, C2.2, C3.2, C4.2, C5.2, C6.2, C7.2, C8.2, C10.2, C11.2, C12.2, C13.2, C14.2, J1.2, J3.6, J4.2, J5.2, J5.3, J6.2, R6.2, R8.2, R14.2, R15.2, SC1.2, SW1.2, SW2.2, TVS1.2, TVS2.2, U1.14, U2.5, U2.6, U2.7, U2.8, U2.9, U2.10, U2.11, U2.12, U2.13, U3.1, U4.1, U4.7, U4.9, U5.1, U6.4
ILIM: R6.1, U4.4
MISO: J3.1, TP1.1, U1.8
ONESHOT_Q: D6.1, U6.5
OS_CEXT: C9.1, U6.6
OS_RC: C9.2, R13.1, U6.7
SCL: J3.3, R3.1, U1.9, U2.16
SDA: J3.4, R2.1, U1.7, U2.15
SOL_OUT1: J2.1, U4.6
SOL_OUT2: J2.2, U4.8
TM_CLK: J4.4, U1.10
TM_DIO: J4.3, U1.6
VBAT1_IN: D1.2, J1.1
VBAT2_IN: D5.2, J6.1
VBAT_CHG: D2.1, R5.2
VBAT_RTC: D2.3, SC1.1, U2.14
VIN_DC: D4.2, J5.1, TVS1.1
VIN_OR: D1.1, D4.1, D5.1, F1.1
VM: C1.1, C2.1, C4.1, C5.1, F1.2, R7.1, TP3.1, TVS2.1, U3.2, U4.5
VM_SENSE: C14.1, R7.2, R8.1, U1.13
